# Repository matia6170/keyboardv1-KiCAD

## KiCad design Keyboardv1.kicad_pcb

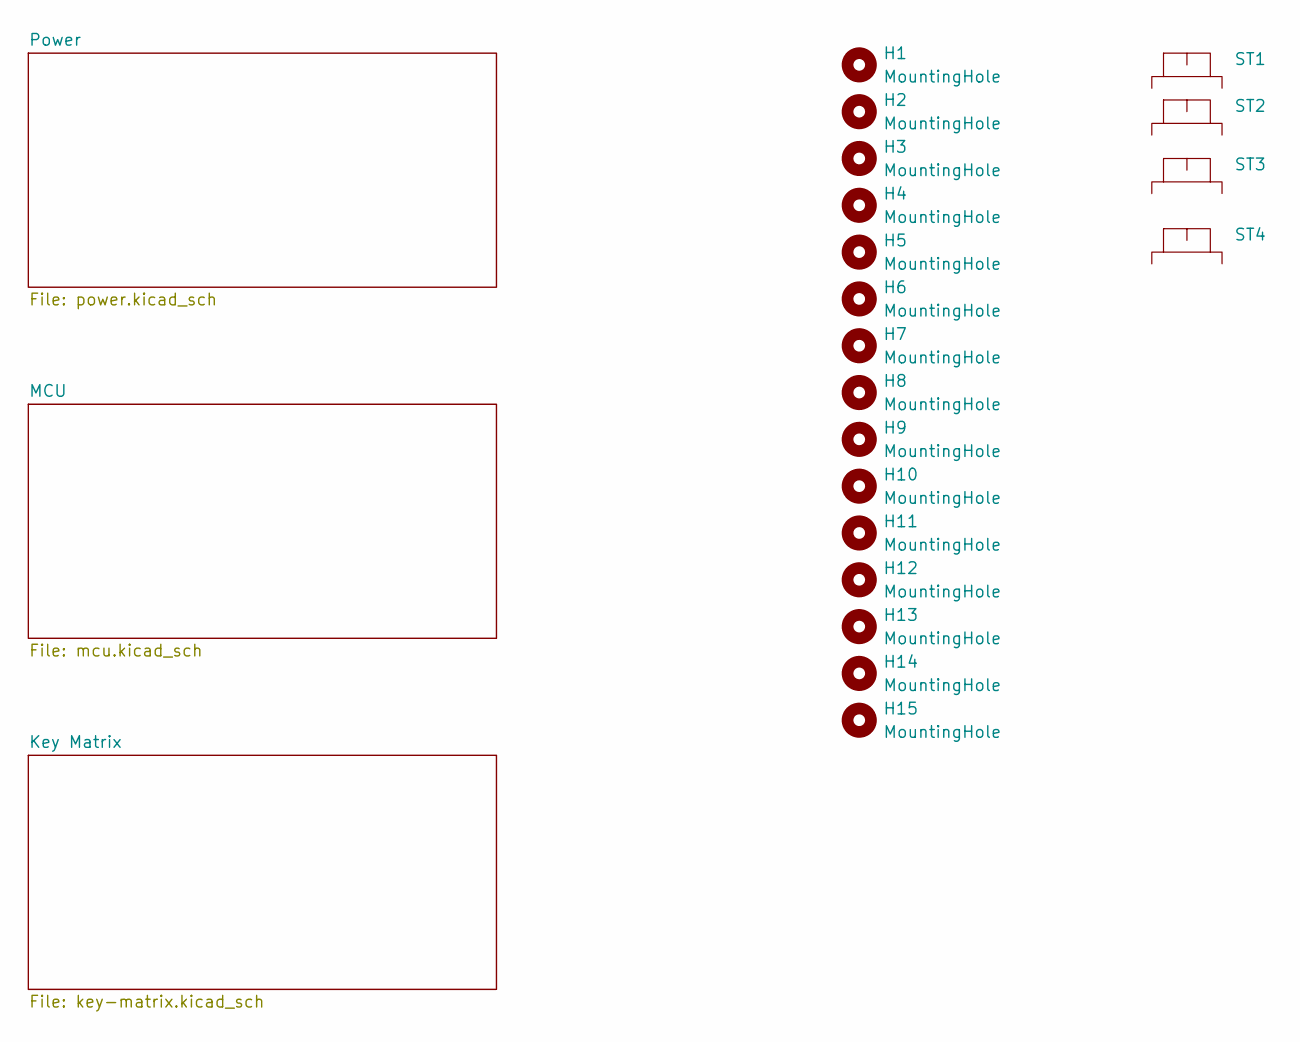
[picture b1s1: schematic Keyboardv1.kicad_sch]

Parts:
H1, H2, H3, H4, H5, H6, H7, H8, H9, H10, H11, H12, H13, H14, H15: MountingHole; MountingHole_3.2mm_M3
ST1, ST2, ST3: Stabilizer_Cherry_MX_2.00u
ST4: Stabilizer_Cherry_MX_6.25u

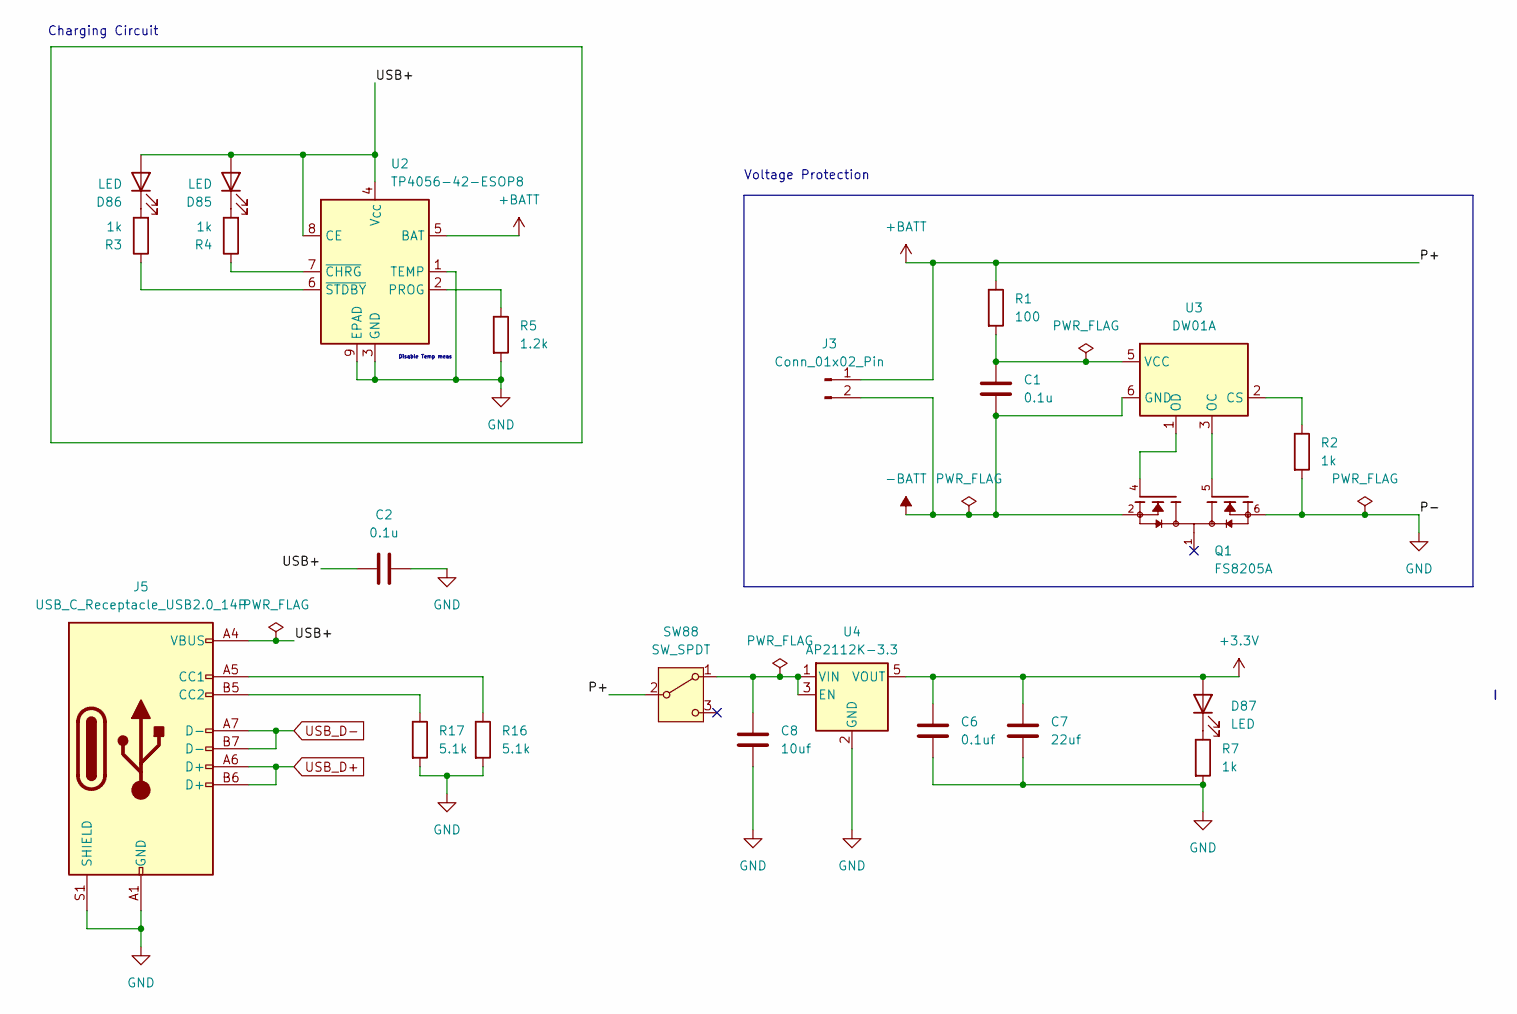
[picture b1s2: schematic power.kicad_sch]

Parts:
C1, C2: 0.1u; C_0805_2012Metric_Pad1.18x1.45mm_HandSolder
C6: 0.1uf; C_0603_1608Metric_Pad1.08x0.95mm_HandSolder
C7: 22uf; C_0603_1608Metric_Pad1.08x0.95mm_HandSolder
C8: 10uf; C_0603_1608Metric_Pad1.08x0.95mm_HandSolder
D85, D86, D87: LED; LED_0805_2012Metric_Pad1.15x1.40mm_HandSolder
J3: Conn_01x02_Pin; JST_PH_B2B-PH-K_1x02_P2.00mm_Vertical
J5: USB_C_Receptacle_USB2.0_14P; USB_C_Receptacle_GCT_USB4105-xx-A_16P_TopMnt_Horizontal
Q1: FS8205A; SOT-23-6; PARTREV 1.7
R1: 100; R_0805_2012Metric_Pad1.20x1.40mm_HandSolder
R2, R3, R4, R7: 1k; R_0805_2012Metric_Pad1.20x1.40mm_HandSolder
R5: 1.2k; R_0805_2012Metric_Pad1.20x1.40mm_HandSolder
R16, R17: 5.1k; R_0603_1608Metric_Pad0.98x0.95mm_HandSolder
SW88: SW_SPDT; SW_Slide_SPDT_Angled_CK_OS102011MA1Q
U2: TP4056-42-ESOP8; SOIC-8-1EP_3.9x4.9mm_P1.27mm_EP2.41x3.3mm_ThermalVias
U3: DW01A; SOT-23-6
U4: AP2112K-3.3; SOT-23-5

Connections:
+3.3V: C6.1, C7.1, D87.2 (A), U4.5 (VOUT); also elsewhere on the board
+BATT: J3.1, R1.1, SW88.2 (B), U2.5 (BAT)
-BATT: C1.2, J3.2, Q1.2, Q1.3, U3.6 (GND)
/Power/USB+: C2.2, D85.2 (A), D86.2 (A), J5.A4 (VBUS), J5.A9 (VBUS), J5.B4 (VBUS), J5.B9 (VBUS), U2.4 (V_{CC}), U2.8 (CE)
GND: C2.1, C6.2, C7.2, C8.2, J5.A1 (GND), J5.A12 (GND), J5.B1 (GND), J5.B12 (GND), J5.S1 (SHIELD), Q1.6, Q1.7, R2.2, R5.2, R7.2, R16.2, R17.2, U2.1 (TEMP), U2.3 (GND), U2.9 (EPAD), U4.2 (GND); also elsewhere on the board
unnamed: D85.1 (K), R4.2
unnamed: D86.1 (K), R3.2
unnamed: D87.1 (K), R7.1
unnamed: J5.A5 (CC1), R16.1
unnamed: J5.B5 (CC2), R17.1
unnamed: C8.1, SW88.1 (A), U4.1 (VIN), U4.3 (EN)
unnamed: R5.1, U2.2 (PROG)
unnamed: R4.1, U2.7 (~CHRG)
unnamed: R3.1, U2.6 (~STDBY)
unnamed: R2.1, U3.2 (CS)
unnamed: Q1.5, U3.3 (OC)
unnamed: Q1.4, U3.1 (OD)
unnamed: C1.1, R1.2, U3.5 (VCC)
USB_D+: J5.A6 (D+), J5.B6 (D+); also elsewhere on the board
USB_D-: J5.A7 (D-), J5.B7 (D-); also elsewhere on the board

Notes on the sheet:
Voltage Protection
Disable Temp meas
Charging Circuit

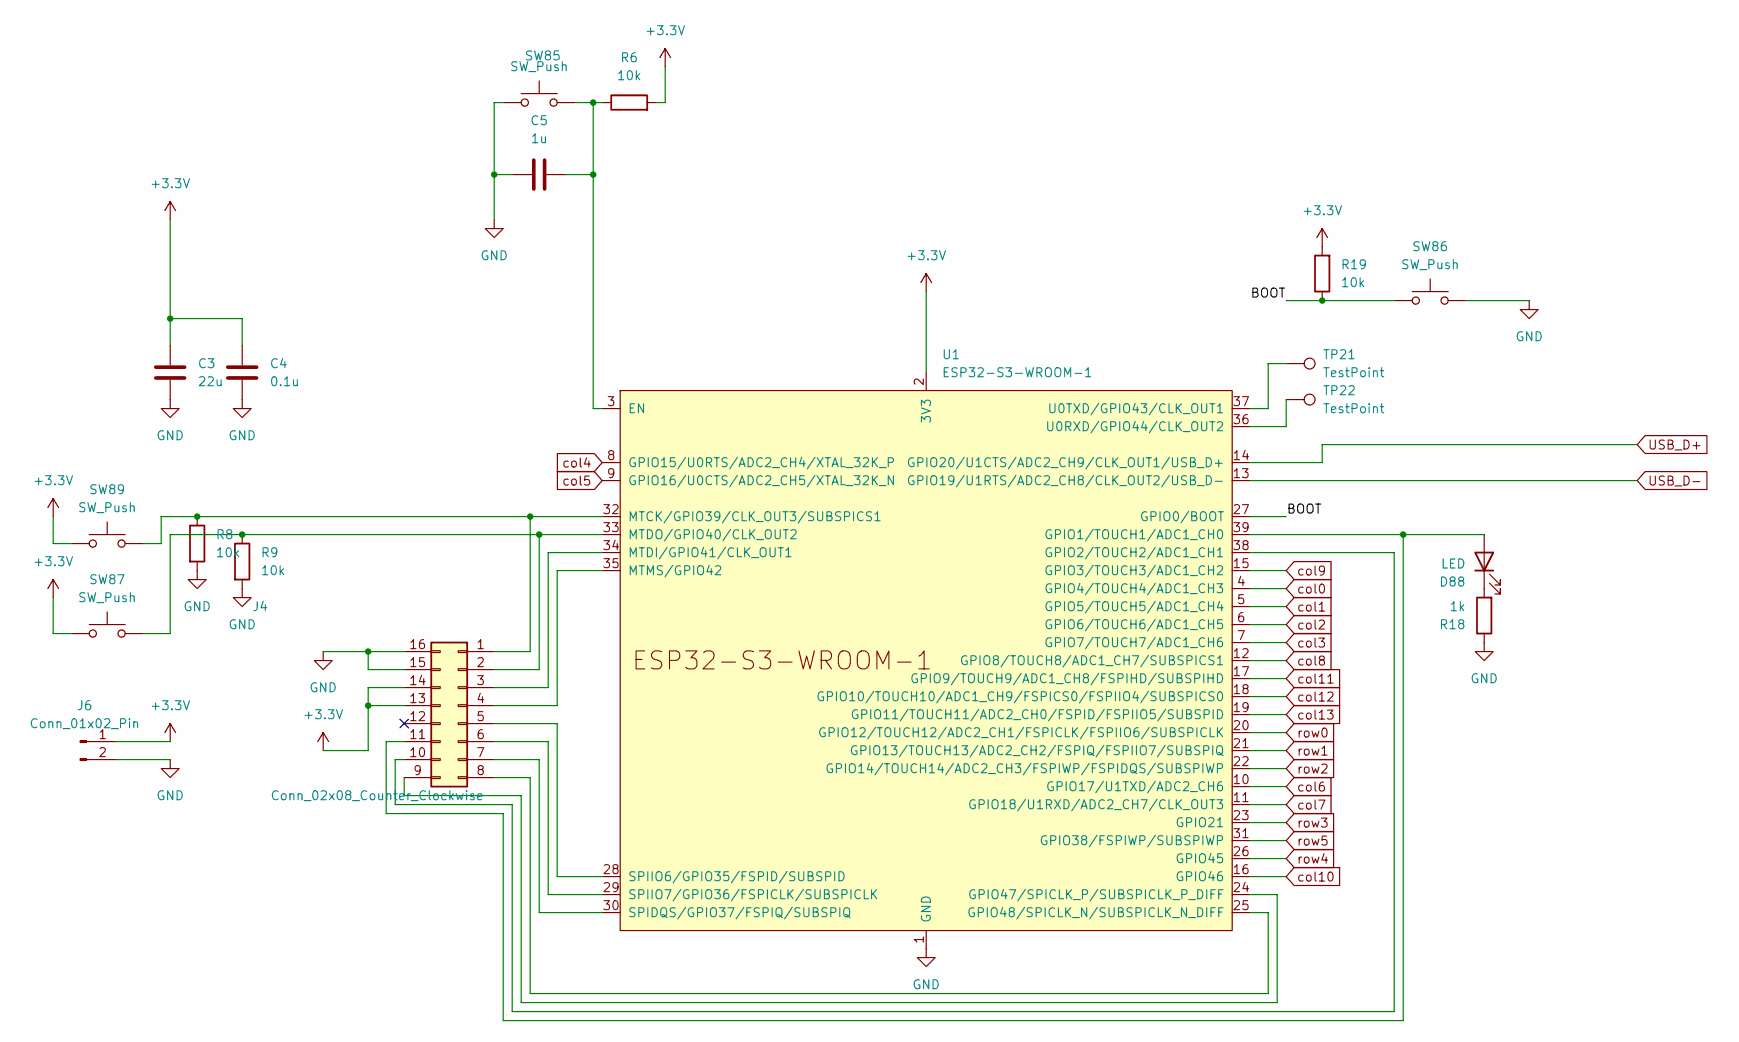
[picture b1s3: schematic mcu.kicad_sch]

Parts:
C3: 22u; C_0805_2012Metric_Pad1.18x1.45mm_HandSolder
C4: 0.1u; C_0805_2012Metric_Pad1.18x1.45mm_HandSolder
C5: 1u; C_0805_2012Metric_Pad1.18x1.45mm_HandSolder
D88: LED; LED_0805_2012Metric_Pad1.15x1.40mm_HandSolder
J4: Conn_02x08_Counter_Clockwise; PinHeader_2x08_P2.54mm_Vertical
J6: Conn_01x02_Pin; PinHeader_1x02_P2.54mm_Vertical
R6, R8, R9, R19: 10k; R_0805_2012Metric_Pad1.20x1.40mm_HandSolder
R18: 1k; R_0805_2012Metric_Pad1.20x1.40mm_HandSolder
SW85, SW86, SW87, SW89: SW_Push; SW_PUSH_6mm
TP21, TP22: TestPoint; TestPoint_Pad_D1.0mm
U1: ESP32-S3-WROOM-1

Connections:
+3.3V: C3.1, C4.1, J4.13, J4.14, J6.1, R6.2, R19.2, SW87.1, SW89.1, U1.2 (3V3); also elsewhere on the board
/MCU/BOOT: R19.1, SW86.1, U1.27 (GPIO0/BOOT)
GND: C3.2, C4.2, C5.1, J4.15, J4.16, J6.2, R8.2, R9.2, R18.1, SW85.1, SW86.2, U1.1 (GND), U1.40 (GND), U1.41 (GND); also elsewhere on the board
unnamed: D88.2 (A), J4.11, U1.39 (GPIO1/TOUCH1/ADC1_CH0)
unnamed: D88.1 (K), R18.2
unnamed: J4.1, R8.1, SW89.2, U1.32 (MTCK/GPIO39/CLK_OUT3/SUBSPICS1)
unnamed: J4.2, R9.1, SW87.2, U1.33 (MTDO/GPIO40/CLK_OUT2)
unnamed: J4.3, U1.34 (MTDI/GPIO41/CLK_OUT1)
unnamed: J4.4, U1.35 (MTMS/GPIO42)
unnamed: J4.5, U1.28 (SPIIO6/GPIO35/FSPID/SUBSPID)
unnamed: J4.6, U1.29 (SPIIO7/GPIO36/FSPICLK/SUBSPICLK)
unnamed: J4.7, U1.30 (SPIDQS/GPIO37/FSPIQ/SUBSPIQ)
unnamed: J4.8, U1.25 (GPIO48/SPICLK_N/SUBSPICLK_N_DIFF)
unnamed: J4.9, U1.24 (GPIO47/SPICLK_P/SUBSPICLK_P_DIFF)
unnamed: J4.10, U1.38 (GPIO2/TOUCH2/ADC1_CH1)
unnamed: C5.2, R6.1, SW85.2, U1.3 (EN)
unnamed: TP22.1, U1.36 (U0RXD/GPIO44/CLK_OUT2)
unnamed: TP21.1, U1.37 (U0TXD/GPIO43/CLK_OUT1)
USB_D+: U1.14 (GPIO20/U1CTS/ADC2_CH9/CLK_OUT1/USB_D+); also elsewhere on the board
USB_D-: U1.13 (GPIO19/U1RTS/ADC2_CH8/CLK_OUT2/USB_D-); also elsewhere on the board
col0: U1.4 (GPIO4/TOUCH4/ADC1_CH3); also elsewhere on the board
col1: U1.5 (GPIO5/TOUCH5/ADC1_CH4); also elsewhere on the board
col2: U1.6 (GPIO6/TOUCH6/ADC1_CH5); also elsewhere on the board
col3: U1.7 (GPIO7/TOUCH7/ADC1_CH6); also elsewhere on the board
col4: U1.8 (GPIO15/U0RTS/ADC2_CH4/XTAL_32K_P); also elsewhere on the board
col5: U1.9 (GPIO16/U0CTS/ADC2_CH5/XTAL_32K_N); also elsewhere on the board
col6: U1.10 (GPIO17/U1TXD/ADC2_CH6); also elsewhere on the board
col7: U1.11 (GPIO18/U1RXD/ADC2_CH7/CLK_OUT3); also elsewhere on the board
col8: U1.12 (GPIO8/TOUCH8/ADC1_CH7/SUBSPICS1); also elsewhere on the board
col9: U1.15 (GPIO3/TOUCH3/ADC1_CH2); also elsewhere on the board
col10: U1.16 (GPIO46); also elsewhere on the board
col11: U1.17 (GPIO9/TOUCH9/ADC1_CH8/FSPIHD/SUBSPIHD); also elsewhere on the board
col12: U1.18 (GPIO10/TOUCH10/ADC1_CH9/FSPICS0/FSPIIO4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); also elsewhere on the board
col13: U1.19 (GPIO11/TOUCH11/ADC2_CH0/FSPID/FSPIIO5/S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); also elsewhere on the board
row0: U1.20 (GPIO12/TOUCH12/ADC2_CH1/FSPICLK/FSPIIO6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); also elsewhere on the board
row1: U1.21 (GPIO13/TOUCH13/ADC2_CH2/FSPIQ/FSPIIO7/S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); also elsewhere on the board
row2: U1.22 (GPIO14/TOUCH14/ADC2_CH3/FSPIWP/FSPIDQS/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); also elsewhere on the board
row3: U1.23 (GPIO21); also elsewhere on the board
row4: U1.26 (GPIO45); also elsewhere on the board
row5: U1.31 (GPIO38/FSPIWP/SUBSPIWP); also elsewhere on the board

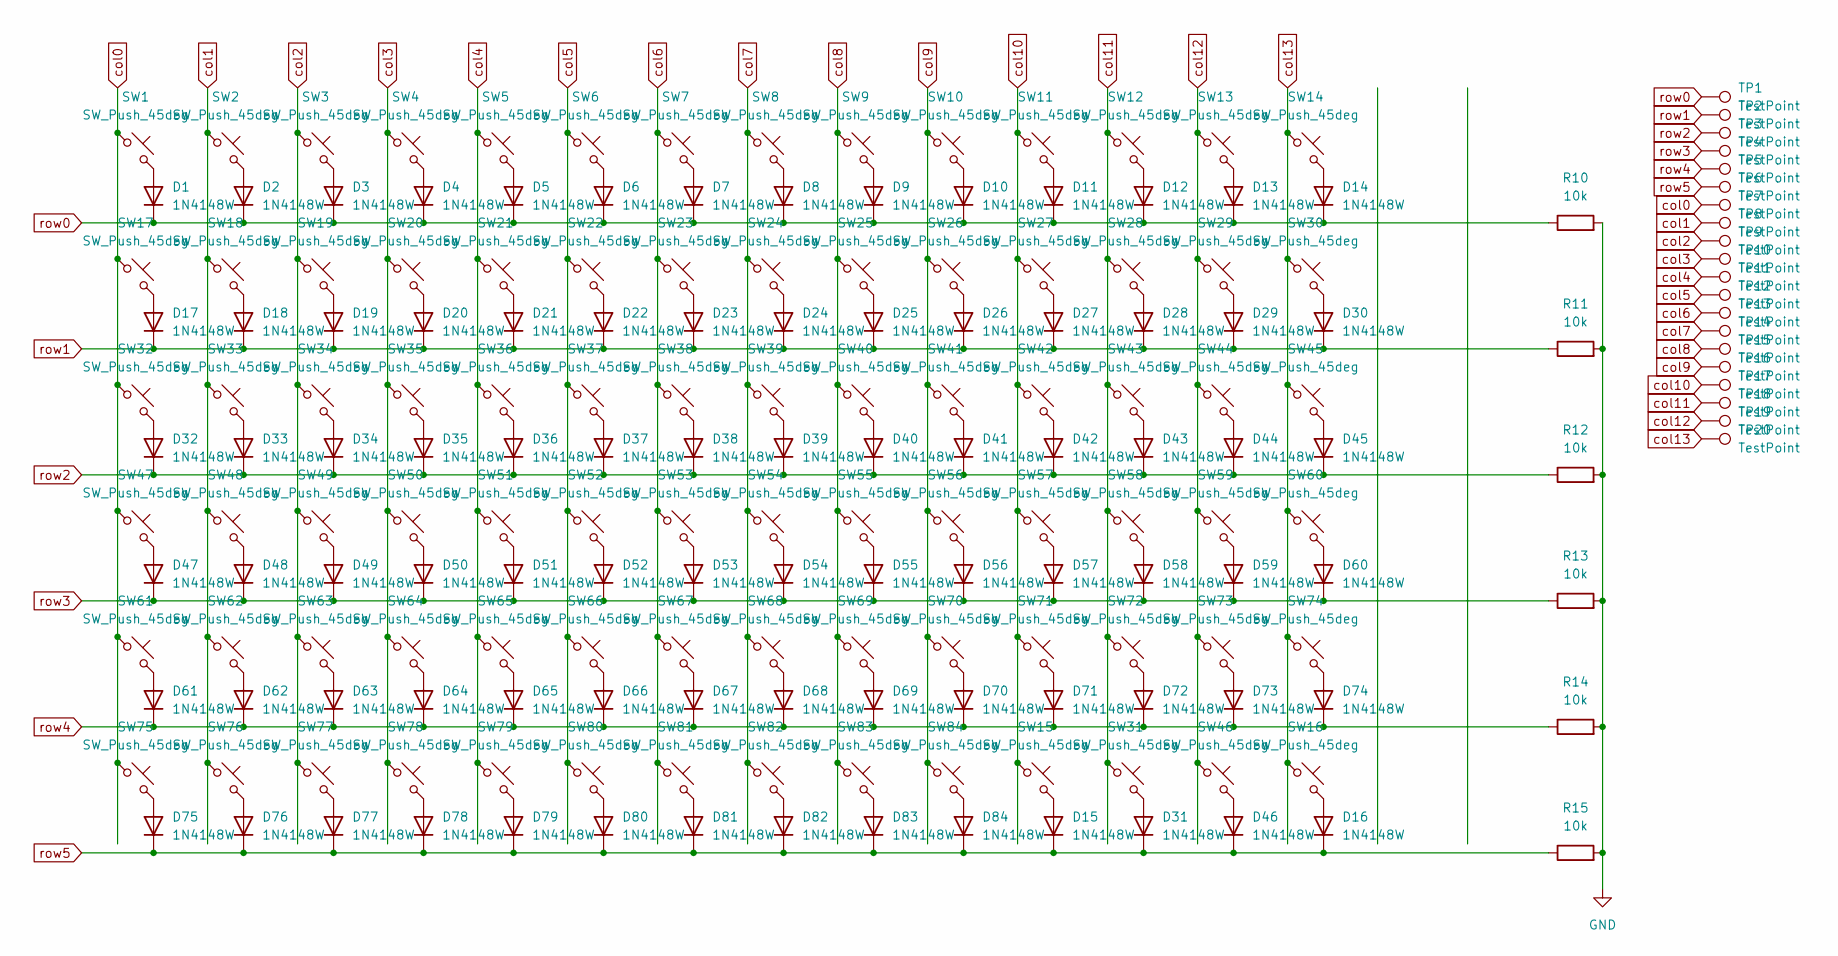
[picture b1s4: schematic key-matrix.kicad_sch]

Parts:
D1, D2, D3, D4, D5, D6, D7, D8, D9, D10, D11, D12, D13, D14, D15, D16, D17, D18, D19, D20, D21, D22, D23, D24, D25, D26, D27, D28, D29, D30, D31, D32, D33, D34, D35, D36, D37, D38, D39, D40, D41, D42, D43, D44, D45, D46, D47, D48, D49, D50, D51, D52, D53, D54, D55, D56, D57, D58, D59, D60, D61, D62, D63, D64, D65, D66, D67, D68, D69, D70, D71, D72, D73, D74, D75, D76, D77, D78, D79, D80, D81, D82, D83, D84: 1N4148W; D_SOD-123
R10, R11, R12, R13, R14, R15: 10k; R_0805_2012Metric_Pad1.20x1.40mm_HandSolder
SW1, SW2, SW3, SW4, SW5, SW6, SW7, SW8, SW9, SW10, SW11, SW12, SW13, SW14, SW15, SW16, SW17, SW18, SW19, SW20, SW21, SW22, SW23, SW24, SW25, SW26, SW27, SW28, SW29, SW30, SW31, SW32, SW33, SW34, SW35, SW36, SW37, SW38, SW39, SW40, SW41, SW42, SW43, SW44, SW45, SW46, SW47, SW48, SW49, SW50, SW51, SW52, SW53, SW54, SW55, SW56, SW57, SW58, SW59, SW60, SW61, SW62, SW63, SW64, SW65, SW66, SW67, SW68, SW69, SW70, SW71, SW72, SW73, SW74, SW75, SW76, SW77, SW78, SW79, SW80, SW81, SW82, SW83, SW84: SW_Push_45deg; SW_Cherry_MX_PCB
TP1, TP2, TP3, TP4, TP5, TP6, TP7, TP8, TP9, TP10, TP11, TP12, TP13, TP14, TP15, TP16, TP17, TP18, TP19, TP20: TestPoint; TestPoint_Pad_D1.0mm

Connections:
GND: R10.2, R11.2, R12.2, R13.2, R14.2, R15.2; also elsewhere on the board
unnamed: D1.2 (A), SW1.2
unnamed: D2.2 (A), SW2.2
unnamed: D3.2 (A), SW3.2
unnamed: D4.2 (A), SW4.2
unnamed: D5.2 (A), SW5.2
unnamed: D6.2 (A), SW6.2
unnamed: D7.2 (A), SW7.2
unnamed: D8.2 (A), SW8.2
unnamed: D9.2 (A), SW9.2
unnamed: D10.2 (A), SW10.2
unnamed: D11.2 (A), SW11.2
unnamed: D12.2 (A), SW12.2
unnamed: D13.2 (A), SW13.2
unnamed: D14.2 (A), SW14.2
unnamed: D15.2 (A), SW15.2
unnamed: D16.2 (A), SW16.2
unnamed: D17.2 (A), SW17.2
unnamed: D18.2 (A), SW18.2
unnamed: D19.2 (A), SW19.2
unnamed: D20.2 (A), SW20.2
unnamed: D21.2 (A), SW21.2
unnamed: D22.2 (A), SW22.2
unnamed: D23.2 (A), SW23.2
unnamed: D24.2 (A), SW24.2
unnamed: D25.2 (A), SW25.2
unnamed: D26.2 (A), SW26.2
unnamed: D27.2 (A), SW27.2
unnamed: D28.2 (A), SW28.2
unnamed: D29.2 (A), SW29.2
unnamed: D30.2 (A), SW30.2
unnamed: D31.2 (A), SW31.2
unnamed: D32.2 (A), SW32.2
unnamed: D33.2 (A), SW33.2
unnamed: D34.2 (A), SW34.2
unnamed: D35.2 (A), SW35.2
unnamed: D36.2 (A), SW36.2
unnamed: D37.2 (A), SW37.2
unnamed: D38.2 (A), SW38.2
unnamed: D39.2 (A), SW39.2
unnamed: D40.2 (A), SW40.2
unnamed: D41.2 (A), SW41.2
unnamed: D42.2 (A), SW42.2
unnamed: D43.2 (A), SW43.2
unnamed: D44.2 (A), SW44.2
unnamed: D45.2 (A), SW45.2
unnamed: D46.2 (A), SW46.2
unnamed: D47.2 (A), SW47.2
unnamed: D48.2 (A), SW48.2
unnamed: D49.2 (A), SW49.2
unnamed: D50.2 (A), SW50.2
unnamed: D51.2 (A), SW51.2
unnamed: D52.2 (A), SW52.2
unnamed: D53.2 (A), SW53.2
unnamed: D54.2 (A), SW54.2
unnamed: D55.2 (A), SW55.2
unnamed: D56.2 (A), SW56.2
unnamed: D57.2 (A), SW57.2
unnamed: D58.2 (A), SW58.2
unnamed: D59.2 (A), SW59.2
unnamed: D60.2 (A), SW60.2
unnamed: D61.2 (A), SW61.2
unnamed: D62.2 (A), SW62.2
unnamed: D63.2 (A), SW63.2
unnamed: D64.2 (A), SW64.2
unnamed: D65.2 (A), SW65.2
unnamed: D66.2 (A), SW66.2
unnamed: D67.2 (A), SW67.2
unnamed: D68.2 (A), SW68.2
unnamed: D69.2 (A), SW69.2
unnamed: D70.2 (A), SW70.2
unnamed: D71.2 (A), SW71.2
unnamed: D72.2 (A), SW72.2
unnamed: D73.2 (A), SW73.2
unnamed: D74.2 (A), SW74.2
unnamed: D75.2 (A), SW75.2
unnamed: D76.2 (A), SW76.2
unnamed: D77.2 (A), SW77.2
unnamed: D78.2 (A), SW78.2
unnamed: D79.2 (A), SW79.2
unnamed: D80.2 (A), SW80.2
unnamed: D81.2 (A), SW81.2
unnamed: D82.2 (A), SW82.2
unnamed: D83.2 (A), SW83.2
unnamed: D84.2 (A), SW84.2
col0: SW1.1, SW17.1, SW32.1, SW47.1, SW61.1, SW75.1, TP7.1; also elsewhere on the board
col1: SW2.1, SW18.1, SW33.1, SW48.1, SW62.1, SW76.1, TP8.1; also elsewhere on the board
col2: SW3.1, SW19.1, SW34.1, SW49.1, SW63.1, SW77.1, TP9.1; also elsewhere on the board
col3: SW4.1, SW20.1, SW35.1, SW50.1, SW64.1, SW78.1, TP10.1; also elsewhere on the board
col4: SW5.1, SW21.1, SW36.1, SW51.1, SW65.1, SW79.1, TP11.1; also elsewhere on the board
col5: SW6.1, SW22.1, SW37.1, SW52.1, SW66.1, SW80.1, TP12.1; also elsewhere on the board
col6: SW7.1, SW23.1, SW38.1, SW53.1, SW67.1, SW81.1, TP13.1; also elsewhere on the board
col7: SW8.1, SW24.1, SW39.1, SW54.1, SW68.1, SW82.1, TP14.1; also elsewhere on the board
col8: SW9.1, SW25.1, SW40.1, SW55.1, SW69.1, SW83.1, TP15.1; also elsewhere on the board
col9: SW10.1, SW26.1, SW41.1, SW56.1, SW70.1, SW84.1, TP16.1; also elsewhere on the board
col10: SW11.1, SW15.1, SW27.1, SW42.1, SW57.1, SW71.1, TP17.1; also elsewhere on the board
col11: SW12.1, SW28.1, SW31.1, SW43.1, SW58.1, SW72.1, TP18.1; also elsewhere on the board
col12: SW13.1, SW29.1, SW44.1, SW46.1, SW59.1, SW73.1, TP19.1; also elsewhere on the board
col13: SW14.1, SW16.1, SW30.1, SW45.1, SW60.1, SW74.1, TP20.1; also elsewhere on the board
row0: D1.1 (K), D2.1 (K), D3.1 (K), D4.1 (K), D5.1 (K), D6.1 (K), D7.1 (K), D8.1 (K), D9.1 (K), D10.1 (K), D11.1 (K), D12.1 (K), D13.1 (K), D14.1 (K), R10.1, TP1.1; also elsewhere on the board
row1: D17.1 (K), D18.1 (K), D19.1 (K), D20.1 (K), D21.1 (K), D22.1 (K), D23.1 (K), D24.1 (K), D25.1 (K), D26.1 (K), D27.1 (K), D28.1 (K), D29.1 (K), D30.1 (K), R11.1, TP2.1; also elsewhere on the board
row2: D32.1 (K), D33.1 (K), D34.1 (K), D35.1 (K), D36.1 (K), D37.1 (K), D38.1 (K), D39.1 (K), D40.1 (K), D41.1 (K), D42.1 (K), D43.1 (K), D44.1 (K), D45.1 (K), R12.1, TP3.1; also elsewhere on the board
row3: D47.1 (K), D48.1 (K), D49.1 (K), D50.1 (K), D51.1 (K), D52.1 (K), D53.1 (K), D54.1 (K), D55.1 (K), D56.1 (K), D57.1 (K), D58.1 (K), D59.1 (K), D60.1 (K), R13.1, TP4.1; also elsewhere on the board
row4: D61.1 (K), D62.1 (K), D63.1 (K), D64.1 (K), D65.1 (K), D66.1 (K), D67.1 (K), D68.1 (K), D69.1 (K), D70.1 (K), D71.1 (K), D72.1 (K), D73.1 (K), D74.1 (K), R14.1, TP5.1; also elsewhere on the board
row5: D15.1 (K), D16.1 (K), D31.1 (K), D46.1 (K), D75.1 (K), D76.1 (K), D77.1 (K), D78.1 (K), D79.1 (K), D80.1 (K), D81.1 (K), D82.1 (K), D83.1 (K), D84.1 (K), R15.1, TP6.1; also elsewhere on the board

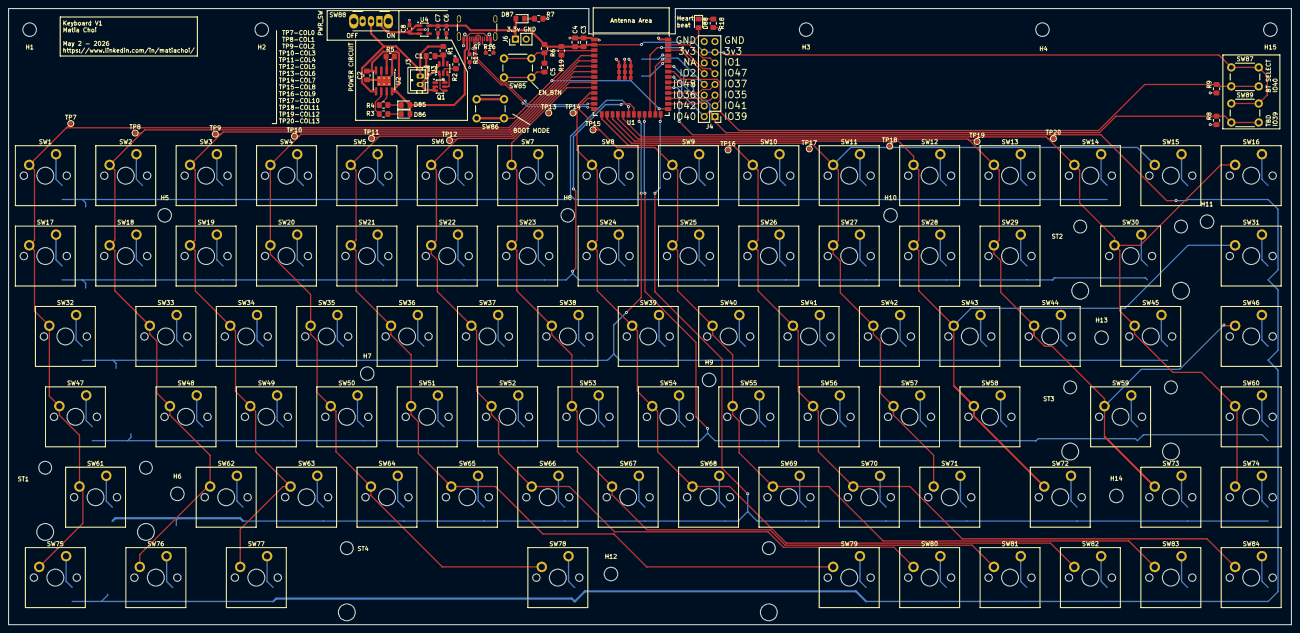
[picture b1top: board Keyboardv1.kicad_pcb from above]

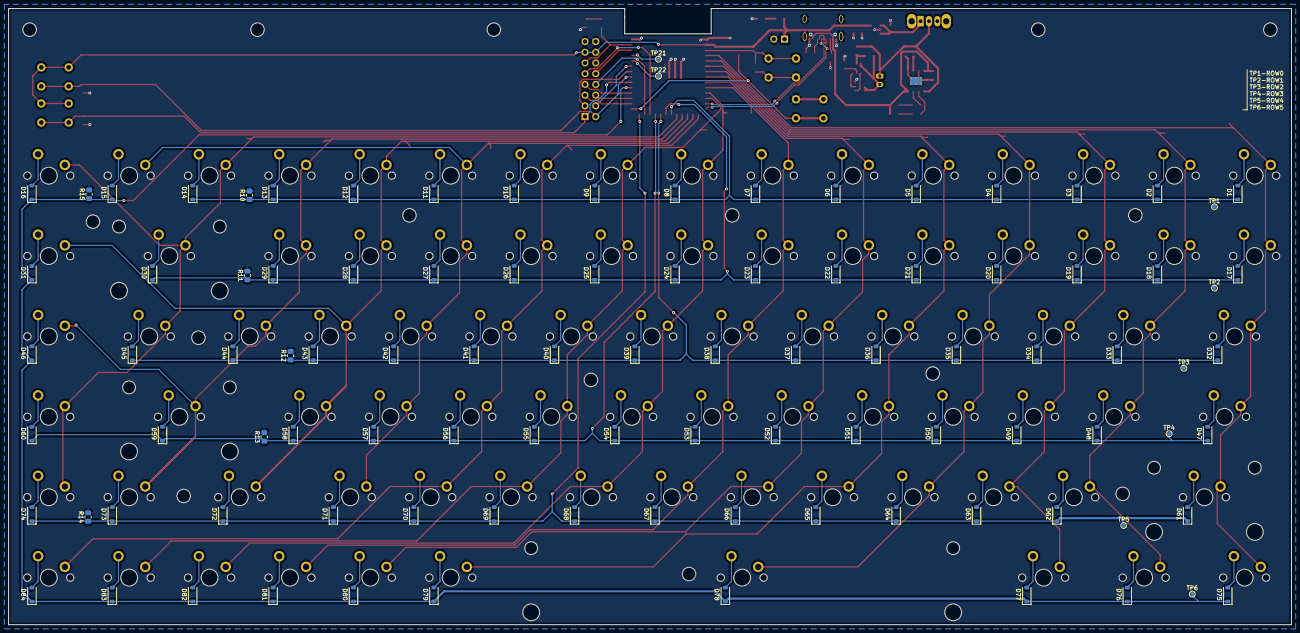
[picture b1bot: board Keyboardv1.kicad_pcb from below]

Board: 2 copper layers, 304.0 x 146.0 mm, 254 parts (98 on the bottom side), 140 nets.

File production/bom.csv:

Designator,Footprint,Quantity,Value,LCSC Part #
"C1, C2, C4",0805,3,0.1u,C28233
C3,0805,1,22u,C45783
C5,0805,1,1u,C28323
C6,0603,1,0.1uf,C14663
C7,0603,1,22uf,C59461
C8,0603,1,10uf,C96446
"D1, D10, D11, D12, D13, D14, D15, D16, D17, D18, D19, D2, D20, D21, D22, D23, D24, D25, D26, D27, D28, D29, D3, D30, D31, D32, D33, D34, D35, D36, D37, D38, D39, D4, D40, D41, D42, D43, D44, D45, D46, D47, D48, D49, D5, D50, D51, D52, D53, D54, D55, D56, D57, D58, D59, D6, D60, D61, D62, D63, D64, D65, D66, D67, D68, D69, D7, D70, D71, D72, D73, D74, D75, D76, D77, D78, D79, D8, D80, D81, D82, D83, D84, D9",D_SOD-123,84,1N4148W,
"D85, D87",0805,2,LED,C84256
D86,0805,1,LED,C2297
D88,0805,1,LED,C34499
J3,JST_PH_B2B-PH-K_1x02_P2.00mm_Vertical,1,Conn_01x02_Pin,
J4,PinHeader_2x08_P2.54mm_Vertical,1,Conn_02x08_Counter_Clockwise,
J5,USB_C_Receptacle_GCT_USB4105-xx-A_16P_TopMnt_Horizontal,1,USB_C_Receptacle_USB2.0_14P,
J6,PinHeader_1x02_P2.54mm_Vertical,1,Conn_01x02_Pin,
Q1,SOT-23-6,1,FS8205A,
R1,0805,1,100,C17408
"R10, R11, R12, R13, R14, R15, R19, R6, R8, R9",0805,10,10k,C17414
"R16, R17",0603,2,5.1k,C23186
"R18, R2, R3, R4, R7",0805,5,1k,C17513
R5,0805,1,1.2k,C17379
"ST1, ST2, ST3",Stabilizer_Cherry_MX_2.00u,3,~,
ST4,Stabilizer_Cherry_MX_6.25u,1,~,
"SW1, SW10, SW11, SW12, SW13, SW14, SW15, SW16, SW17, SW18, SW19, SW2, SW20, SW21, SW22, SW23, SW24, SW25, SW26, SW27, SW28, SW29, SW3, SW30, SW31, SW32, SW33, SW34, SW35, SW36, SW37, SW38, SW39, SW4, SW40, SW41, SW42, SW43, SW44, SW45, SW46, SW47, SW48, SW49, SW5, SW50, SW51, SW52, SW53, SW54, SW55, SW56, SW57, SW58, SW59, SW6, SW60, SW61, SW62, SW63, SW64, SW65, SW66, SW67, SW68, SW69, SW7, SW70, SW71, SW72, SW73, SW74, SW75, SW76, SW77, SW78, SW79, SW8, SW80, SW81, SW82, SW83, SW84, SW9",SW_Cherry_MX_PCB,84,SW_Push_45deg,
"SW85, SW86, SW87, SW89",SW_PUSH_6mm,4,SW_Push,
SW88,SW_Slide_SPDT_Angled_CK_OS102011MA1Q,1,SW_SPDT,
"TP1, TP10, TP11, TP12, TP13, TP14, TP15, TP16, TP17, TP18, TP19, TP2, TP20, TP21, TP22, TP3, TP4, TP5, TP6, TP7, TP8, TP9",TestPoint_Pad_D1.0mm,22,TestPoint,
U1,ESP32-S3-WROOM-1,1,ESP32-S3-WROOM-1,
U2,SOIC-8-1EP_3.9x4.9mm_P1.27mm_EP2.41x3.3mm_ThermalVias,1,TP4056-42-ESOP8,
U3,SOT-23-6,1,DW01A,C351410
U4,SOT-23-5,1,AP2112K-3.3,C51118

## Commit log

2025-12-13 created the keycool84 keyboard matrix schematic and pcb layout only
2026-02-14 chore: remove KiCad backup zips and update gitignore
2026-02-16 almost done
2026-03-31 added more leds pins, fixed rule errors.
2026-04-09 udate
2026-05-03 sent to fab
